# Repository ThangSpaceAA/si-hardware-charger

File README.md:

# st-hardware-charger
phần cứng mạch sạc pin năng lượng mặt trời

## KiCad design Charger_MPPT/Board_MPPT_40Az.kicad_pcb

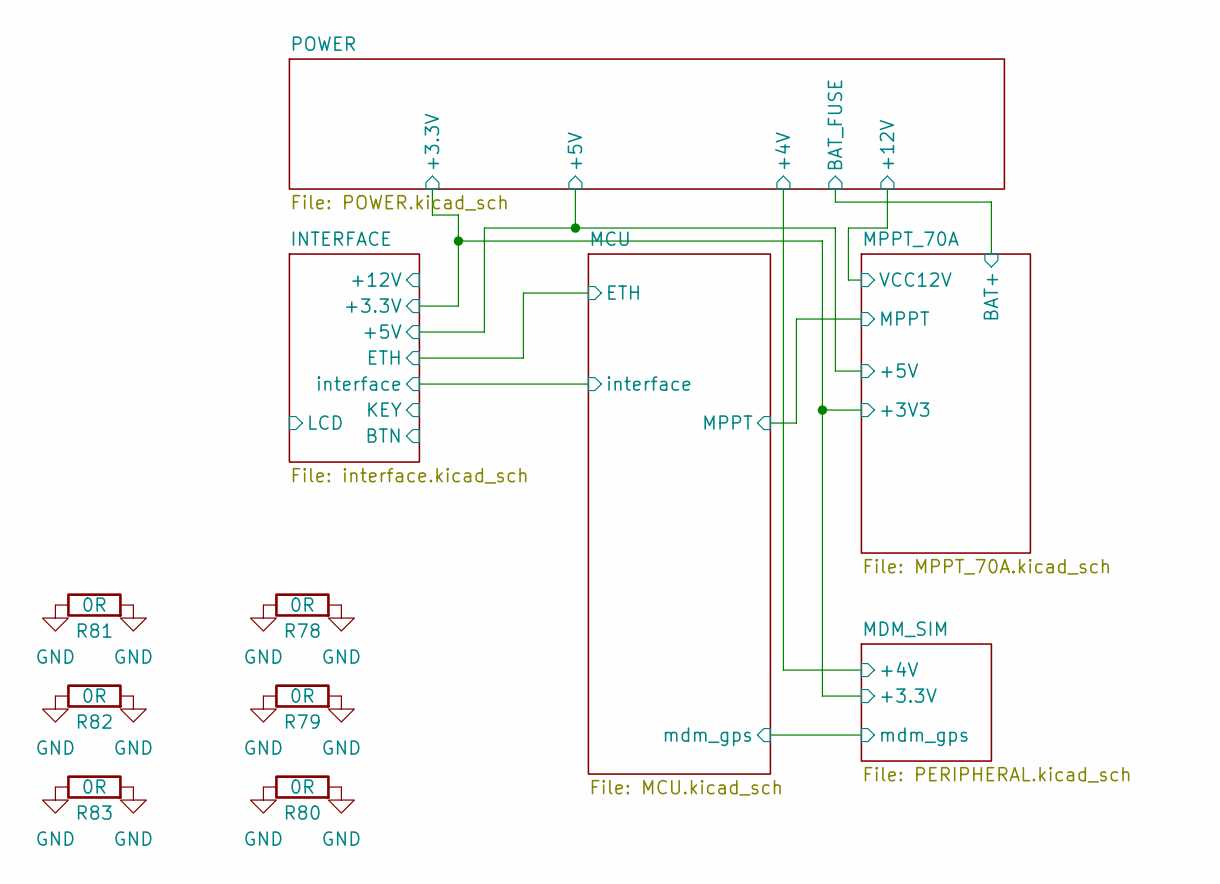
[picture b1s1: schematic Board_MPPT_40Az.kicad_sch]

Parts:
R78, R79, R80, R81, R82, R83: 0R; R_1206_3216Metric

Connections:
GND: R78.1, R78.2, R79.1, R79.2, R80.1, R80.2, R81.1, R81.2, R82.1, R82.2, R83.1, R83.2; also elsewhere on the board

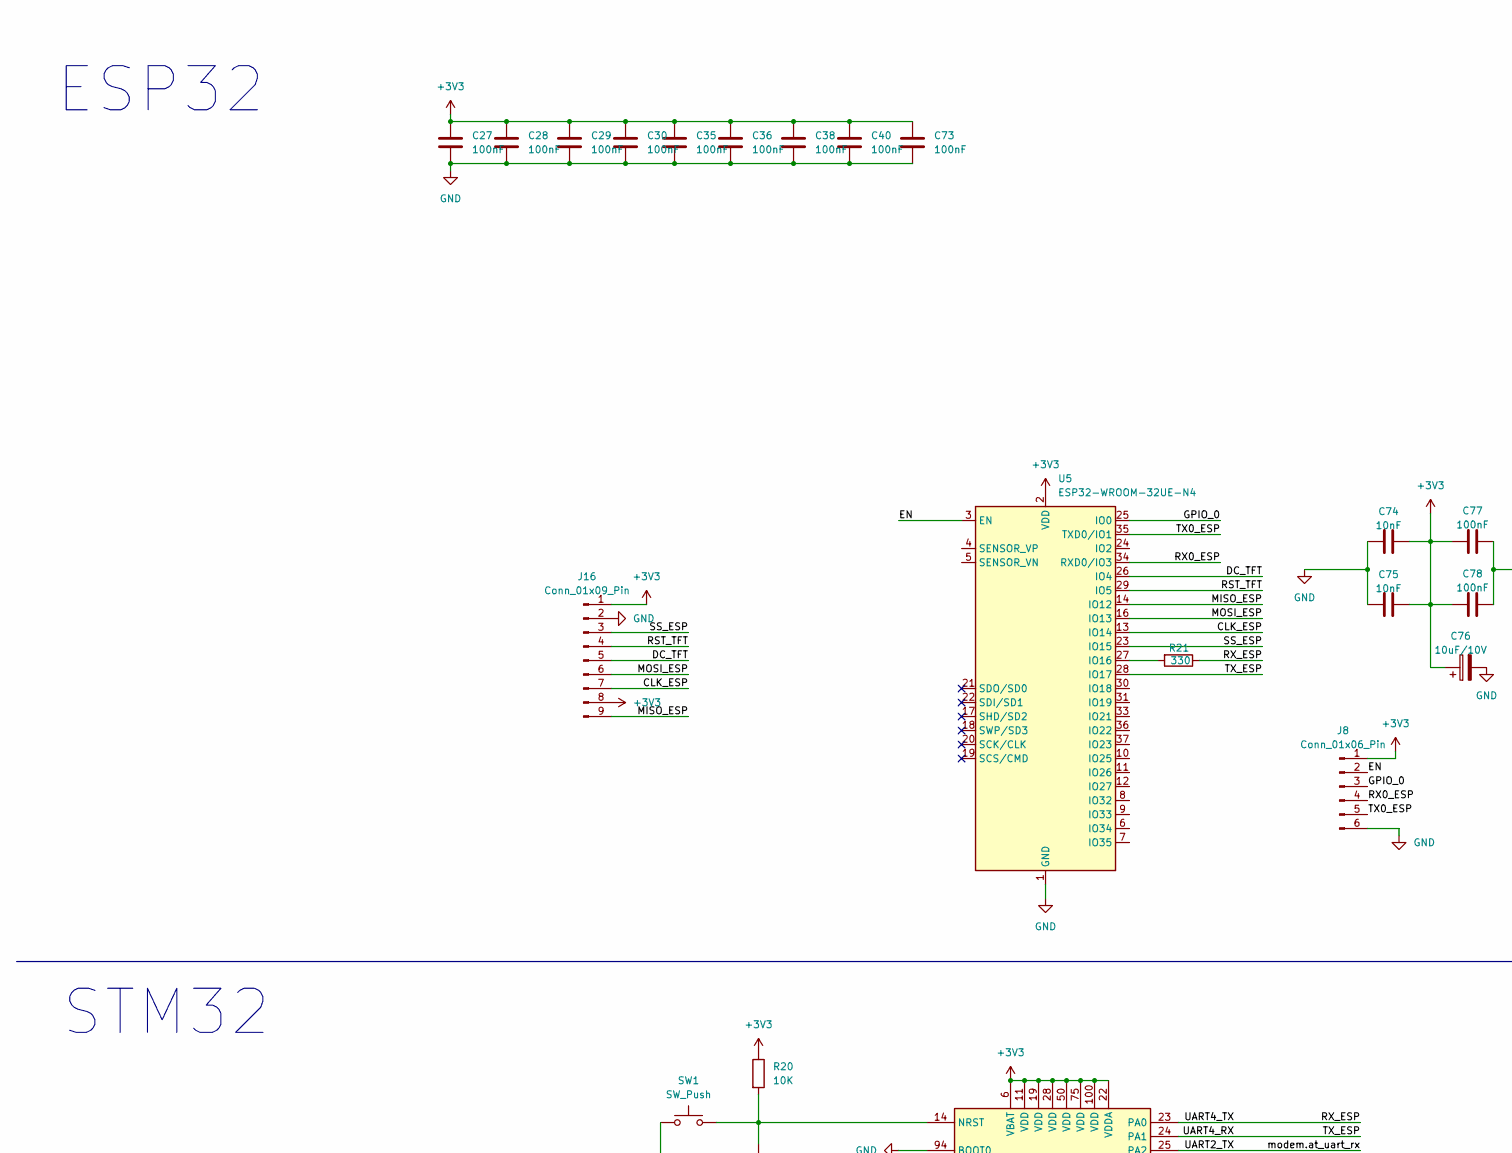
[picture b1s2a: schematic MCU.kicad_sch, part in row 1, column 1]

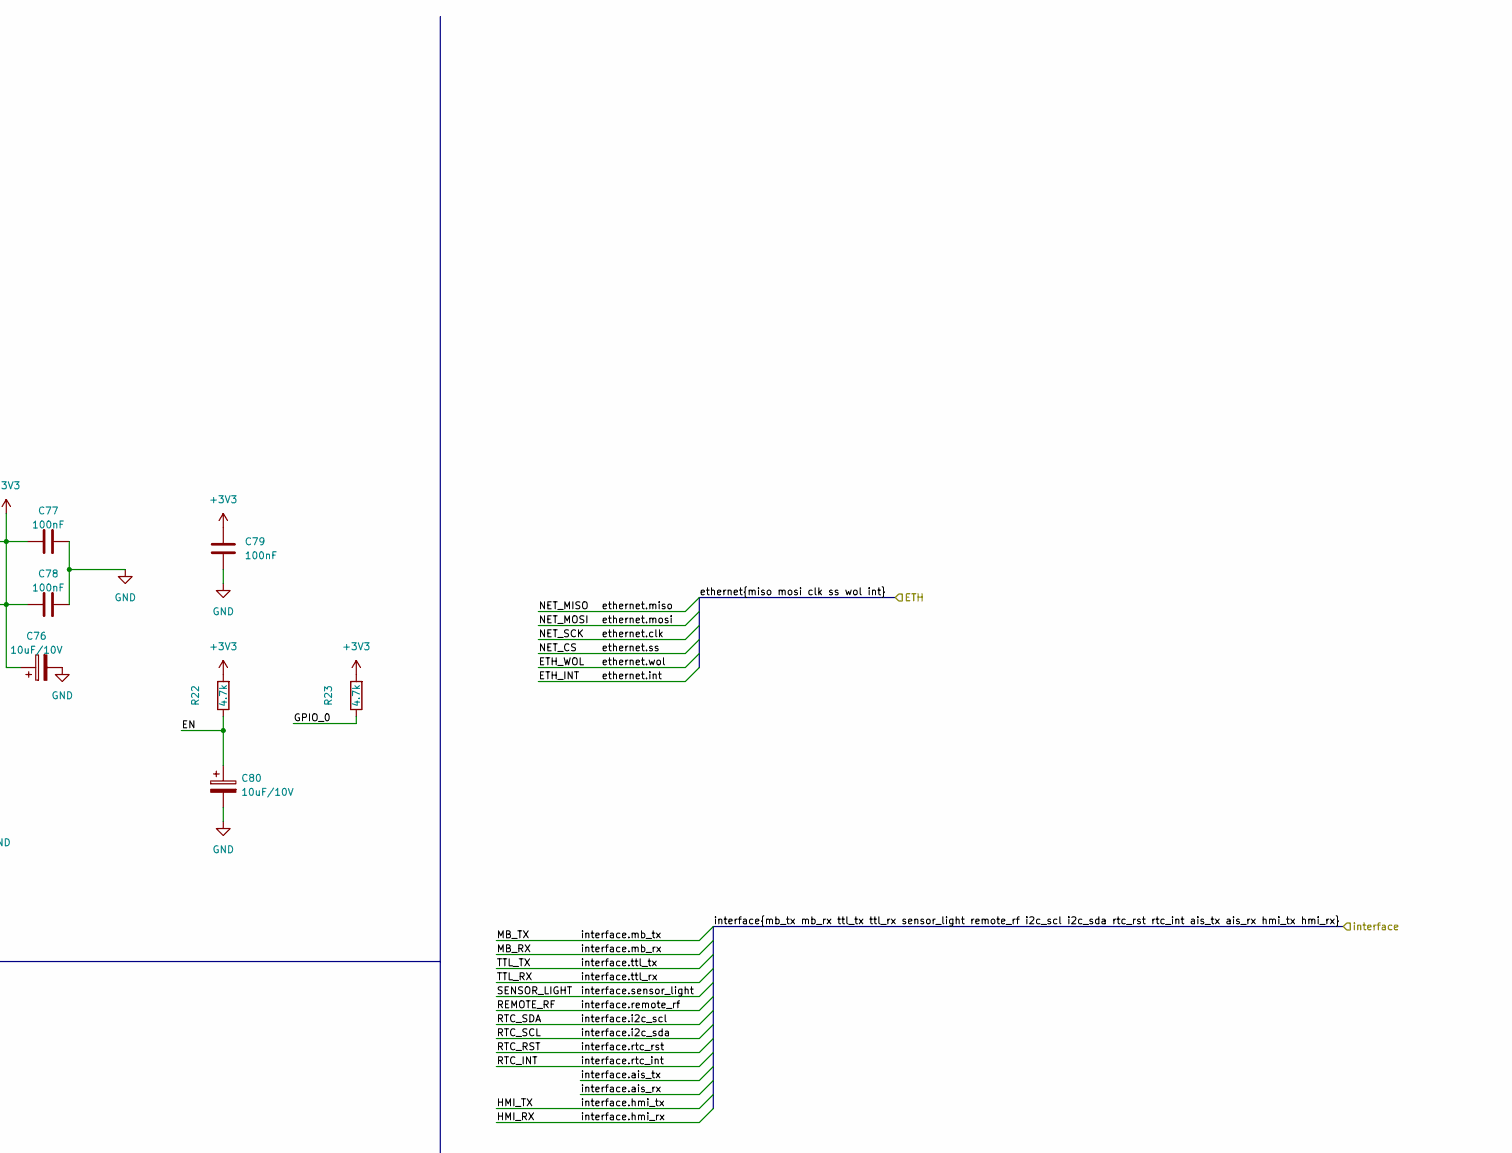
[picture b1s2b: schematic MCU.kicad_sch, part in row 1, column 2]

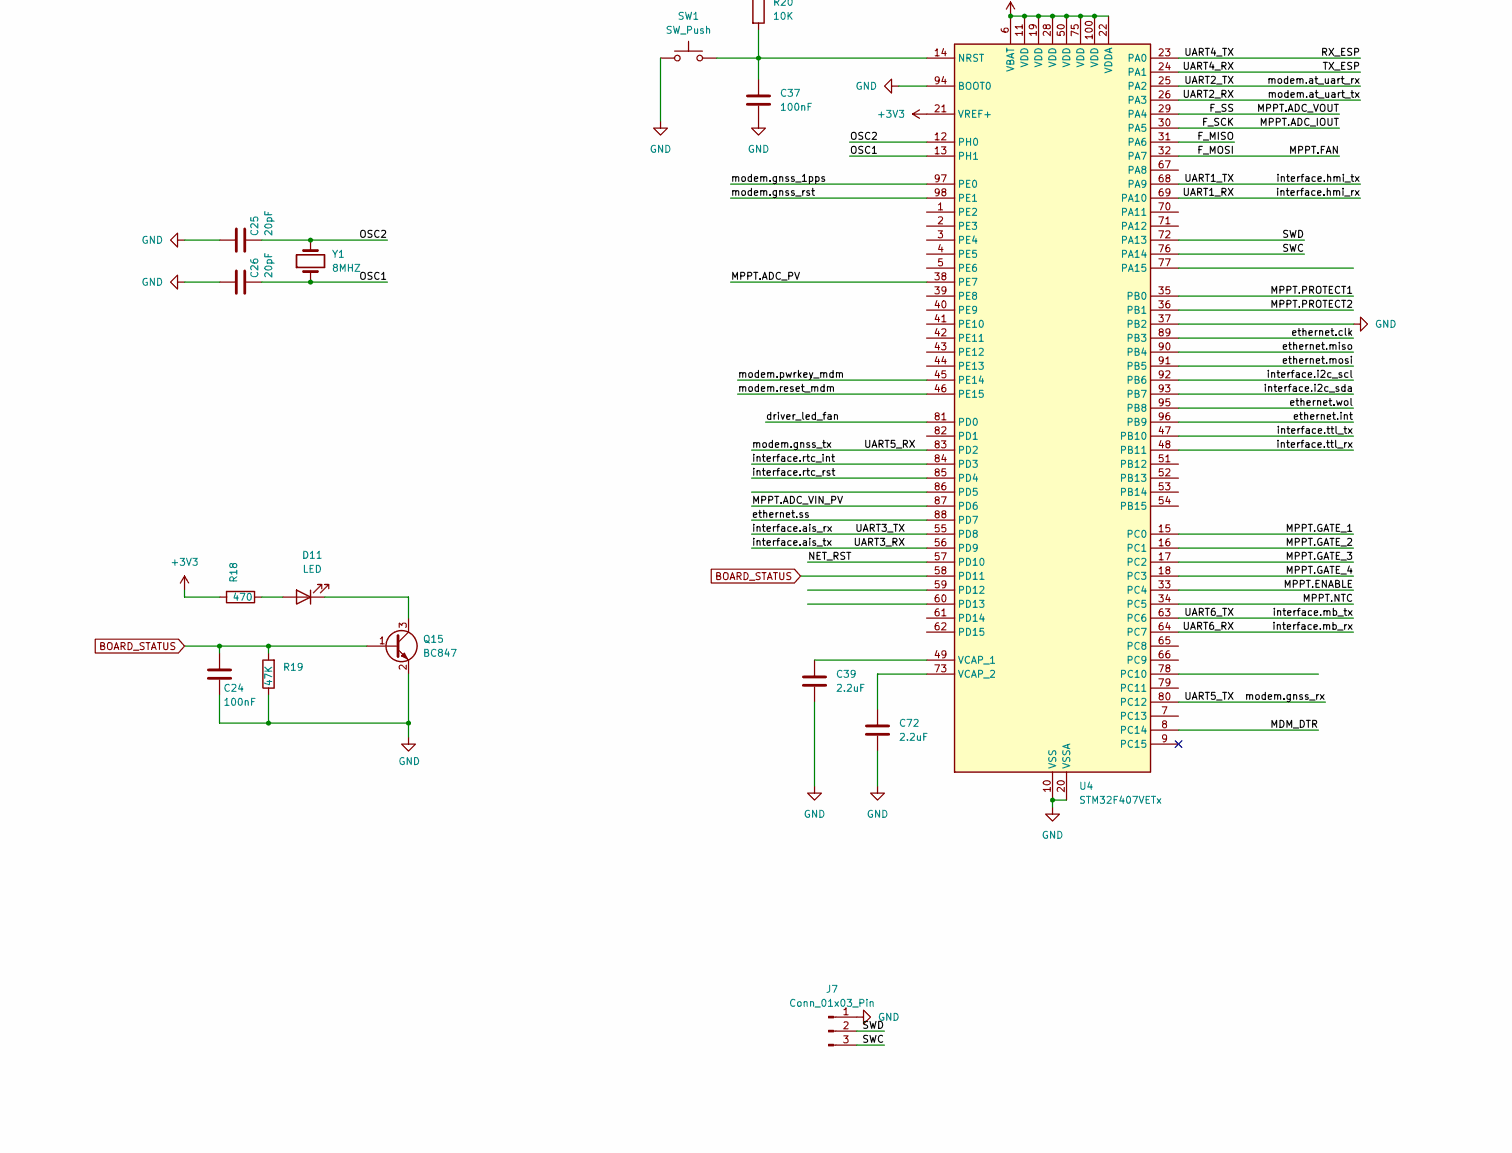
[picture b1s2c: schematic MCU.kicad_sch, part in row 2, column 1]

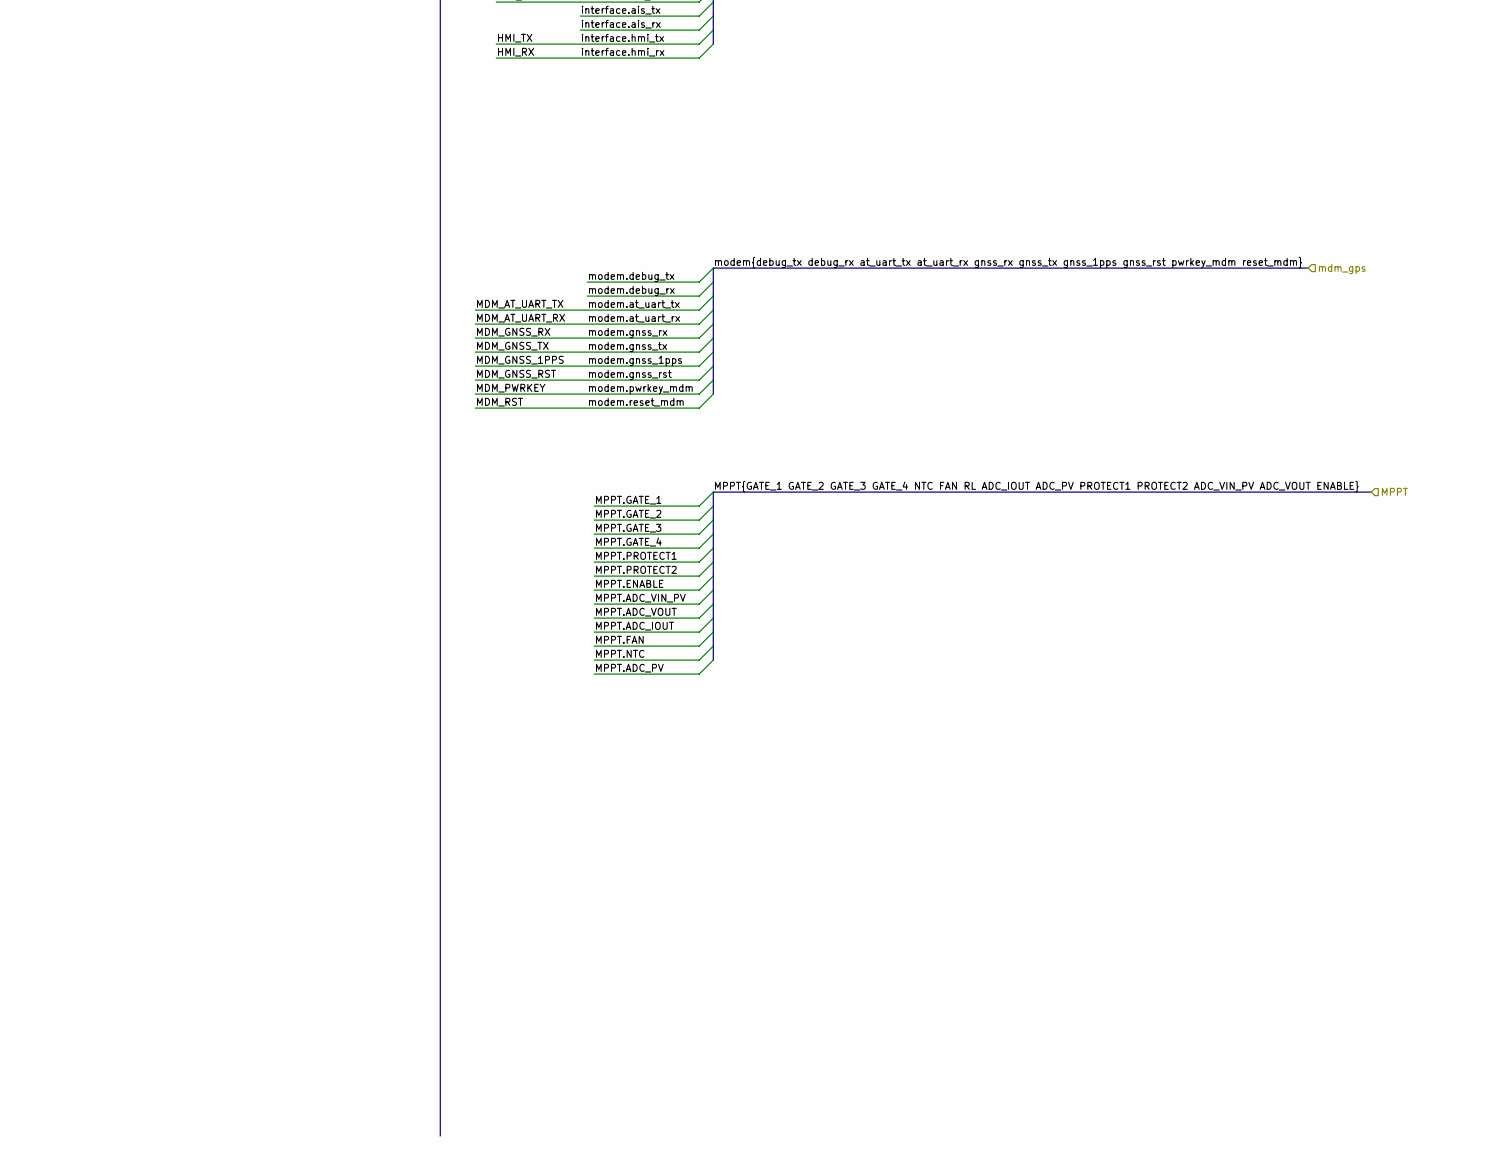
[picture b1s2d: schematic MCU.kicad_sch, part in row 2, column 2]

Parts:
C24, C27, C28, C29, C30, C35, C36, C37, C38, C40, C73, C77, C78, C79: 100nF; C_0805_2012Metric
C25, C26: 20pF; C_0402_1005Metric
C39, C72: 2.2uF; C_0805_2012Metric
C74, C75: 10nF; C_0805_2012Metric
C76, C80: 10uF/10V; CP_EIA-3216-18_Kemet-A
D11: LED; LED_0805_2012Metric
J7: Conn_01x03_Pin; PinHeader_1x03_P2.54mm_Vertical
J8: Conn_01x06_Pin; PinHeader_1x06_P2.54mm_Vertical
J16: Conn_01x09_Pin; PinHeader_1x09_P2.54mm_Vertical
Q15: BC847; SOT-23
R18: 470; R_0805_2012Metric
R19: 47K; R_0805_2012Metric
R20: 10K; R_0805_2012Metric
R21: 330; R_0805_2012Metric
R22, R23: 4.7k; R_0603_1608Metric
SW1: SW_Push; SW_SPST_CK_RS282G05A3
U4: STM32F407VETx; LQFP-100_14x14mm_P0.5mm
U5: ESP32-WROOM-32UE-N4; ESP32-WROOM-32U
Y1: 8MHZ; Crystal_SMD_Abracon_ABM7-2Pin_6.0x3.5mm

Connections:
+3V3: C27.1, C28.1, C29.1, C30.1, C35.1, C36.1, C38.1, C40.1, C73.1, C74.2, C75.2, C76.1, C77.1, C78.1, C79.2, J8.1, J16.1, J16.8, R18.2, R20.1, R22.2, R23.2, U4.6 (VBAT), U4.11 (VDD), U4.19 (VDD), U4.21 (VREF+), U4.22 (VDDA), U4.28 (VDD), U4.50 (VDD), U4.75 (VDD), U4.100 (VDD), U5.2 (VDD); also elsewhere on the board
/INTERFACE/ethernet.clk: U4.89 (PB3); also elsewhere on the board
/INTERFACE/ethernet.int: U4.96 (PB9); also elsewhere on the board
/INTERFACE/ethernet.miso: U4.90 (PB4); also elsewhere on the board
/INTERFACE/ethernet.mosi: U4.91 (PB5); also elsewhere on the board
/INTERFACE/ethernet.ss: U4.88 (PD7); also elsewhere on the board
/INTERFACE/ethernet.wol: U4.95 (PB8); also elsewhere on the board
/INTERFACE/interface.ais_rx: U4.55 (PD8); also elsewhere on the board
/INTERFACE/interface.ais_tx: U4.56 (PD9); also elsewhere on the board
/INTERFACE/interface.hmi_rx: U4.69 (PA10); also elsewhere on the board
/INTERFACE/interface.hmi_tx: U4.68 (PA9); also elsewhere on the board
/INTERFACE/interface.i2c_scl: U4.92 (PB6); also elsewhere on the board
/INTERFACE/interface.i2c_sda: U4.93 (PB7); also elsewhere on the board
/INTERFACE/interface.mb_rx: U4.64 (PC7); also elsewhere on the board
/INTERFACE/interface.mb_tx: U4.63 (PC6); also elsewhere on the board
/INTERFACE/interface.rtc_int: U4.84 (PD3); also elsewhere on the board
/INTERFACE/interface.rtc_rst: U4.85 (PD4); also elsewhere on the board
/INTERFACE/interface.ttl_rx: U4.48 (PB11); also elsewhere on the board
/INTERFACE/interface.ttl_tx: U4.47 (PB10); also elsewhere on the board
/MCU/CLK_ESP: J16.7, U5.13 (IO14)
/MCU/DC_TFT: J16.5, U5.26 (IO4)
/MCU/EN: C80.1, J8.2, R22.1, U5.3 (EN)
/MCU/F_MISO: U4.31 (PA6)
/MCU/GPIO_0: J8.3, R23.1, U5.25 (IO0)
/MCU/MDM_DTR: U4.8 (PC14)
/MCU/MISO_ESP: J16.9, U5.14 (IO12)
/MCU/MOSI_ESP: J16.6, U5.16 (IO13)
/MCU/MPPT.ADC_IOUT: U4.30 (PA5); also elsewhere on the board
/MCU/MPPT.ADC_PV: U4.38 (PE7); also elsewhere on the board
/MCU/MPPT.ADC_VIN_PV: U4.87 (PD6); also elsewhere on the board
/MCU/MPPT.ADC_VOUT: U4.29 (PA4); also elsewhere on the board
/MCU/MPPT.ENABLE: U4.33 (PC4); also elsewhere on the board
/MCU/MPPT.FAN: U4.32 (PA7); also elsewhere on the board
/MCU/MPPT.GATE_1: U4.15 (PC0); also elsewhere on the board
/MCU/MPPT.GATE_2: U4.16 (PC1); also elsewhere on the board
/MCU/MPPT.GATE_3: U4.17 (PC2); also elsewhere on the board
/MCU/MPPT.GATE_4: U4.18 (PC3); also elsewhere on the board
/MCU/MPPT.NTC: U4.34 (PC5); also elsewhere on the board
/MCU/MPPT.PROTECT1: U4.35 (PB0); also elsewhere on the board
/MCU/MPPT.PROTECT2: U4.36 (PB1); also elsewhere on the board
/MCU/NET_RST: U4.57 (PD10)
/MCU/OSC1: C26.2, U4.13 (PH1), Y1.1
/MCU/OSC2: C25.2, U4.12 (PH0), Y1.2
/MCU/RST_TFT: J16.4, U5.29 (IO5)
/MCU/RX0_ESP: J8.4, U5.34 (RXD0/IO3)
/MCU/RX_ESP: R21.1, U4.23 (PA0)
/MCU/SS_ESP: J16.3, U5.23 (IO15)
/MCU/SWC: J7.3, U4.76 (PA14)
/MCU/SWD: J7.2, U4.72 (PA13)
/MCU/TX0_ESP: J8.5, U5.35 (TXD0/IO1)
/MCU/TX_ESP: U4.24 (PA1), U5.28 (IO17)
/MCU/driver_led_fan: U4.81 (PD0)
/MCU/modem.at_uart_rx: U4.25 (PA2); also elsewhere on the board
/MCU/modem.at_uart_tx: U4.26 (PA3); also elsewhere on the board
/MCU/modem.gnss_1pps: U4.97 (PE0); also elsewhere on the board
/MCU/modem.gnss_rst: U4.98 (PE1); also elsewhere on the board
/MCU/modem.gnss_rx: U4.80 (PC12); also elsewhere on the board
/MCU/modem.gnss_tx: U4.83 (PD2); also elsewhere on the board
/MCU/modem.pwrkey_mdm: U4.45 (PE14); also elsewhere on the board
/MCU/modem.reset_mdm: U4.46 (PE15); also elsewhere on the board
BOARD_STATUS: C24.1, Q15.1 (B), R19.2, U4.58 (PD11)
GND: C24.2, C25.1, C26.1, C27.2, C28.2, C29.2, C30.2, C35.2, C36.2, C37.2, C38.2, C39.2, C40.2, C72.2, C73.2, C74.1, C75.1, C76.2, C77.2, C78.2, C79.1, C80.2, J7.1, J8.6, J16.2, Q15.2 (E), R19.1, SW1.1, U4.10 (VSS), U4.20 (VSSA), U4.27 (VSS), U4.37 (PB2), U4.74 (VSS), U4.94 (BOOT0), U4.99 (VSS), U5.1 (GND), U5.15 (GND), U5.38 (GND), U5.39 (GND); also elsewhere on the board
unnamed: D11.2 (A), R18.1
unnamed: D11.1 (K), Q15.3 (C)
unnamed: C37.1, R20.2, SW1.2, U4.14 (NRST)
unnamed: C39.1, U4.49 (VCAP_1)
unnamed: C72.1, U4.73 (VCAP_2)
unnamed: R21.2, U5.27 (IO16)

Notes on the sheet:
ESP32
STM32

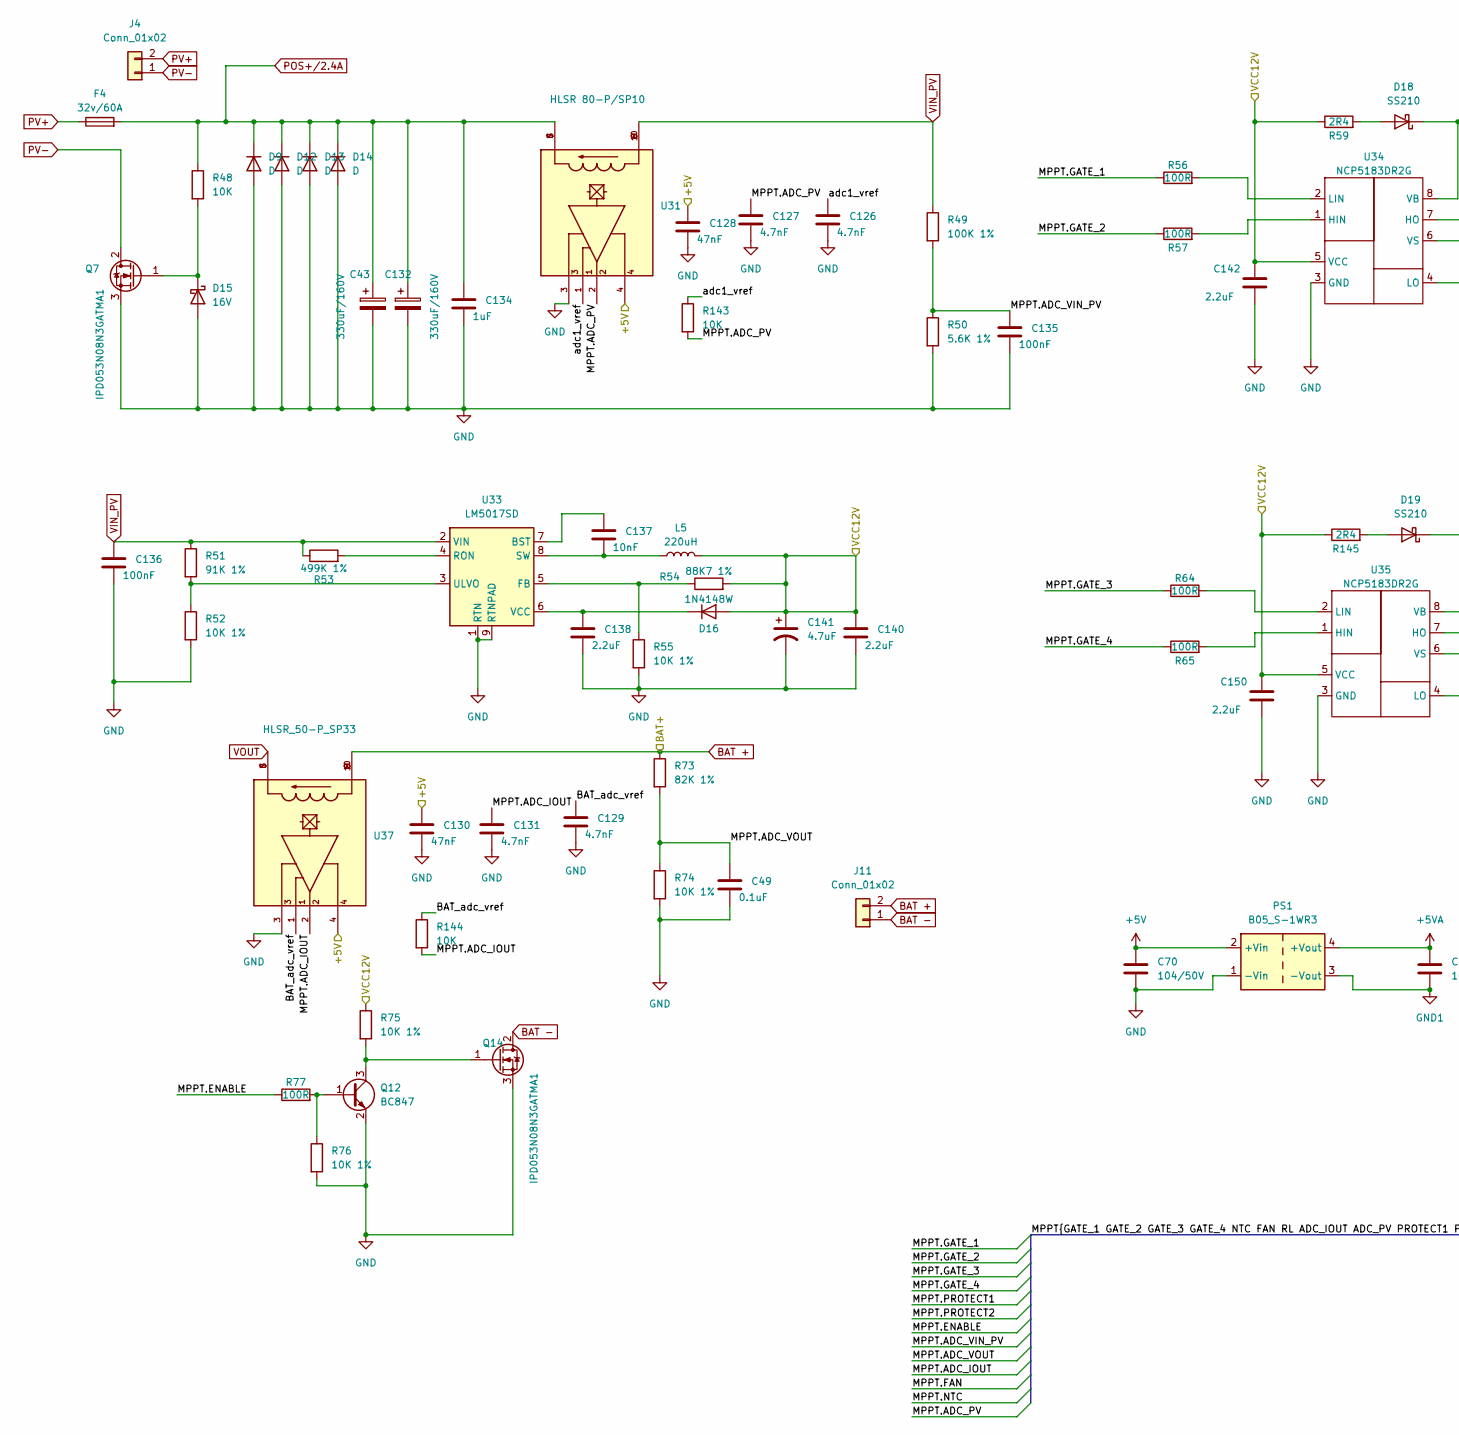
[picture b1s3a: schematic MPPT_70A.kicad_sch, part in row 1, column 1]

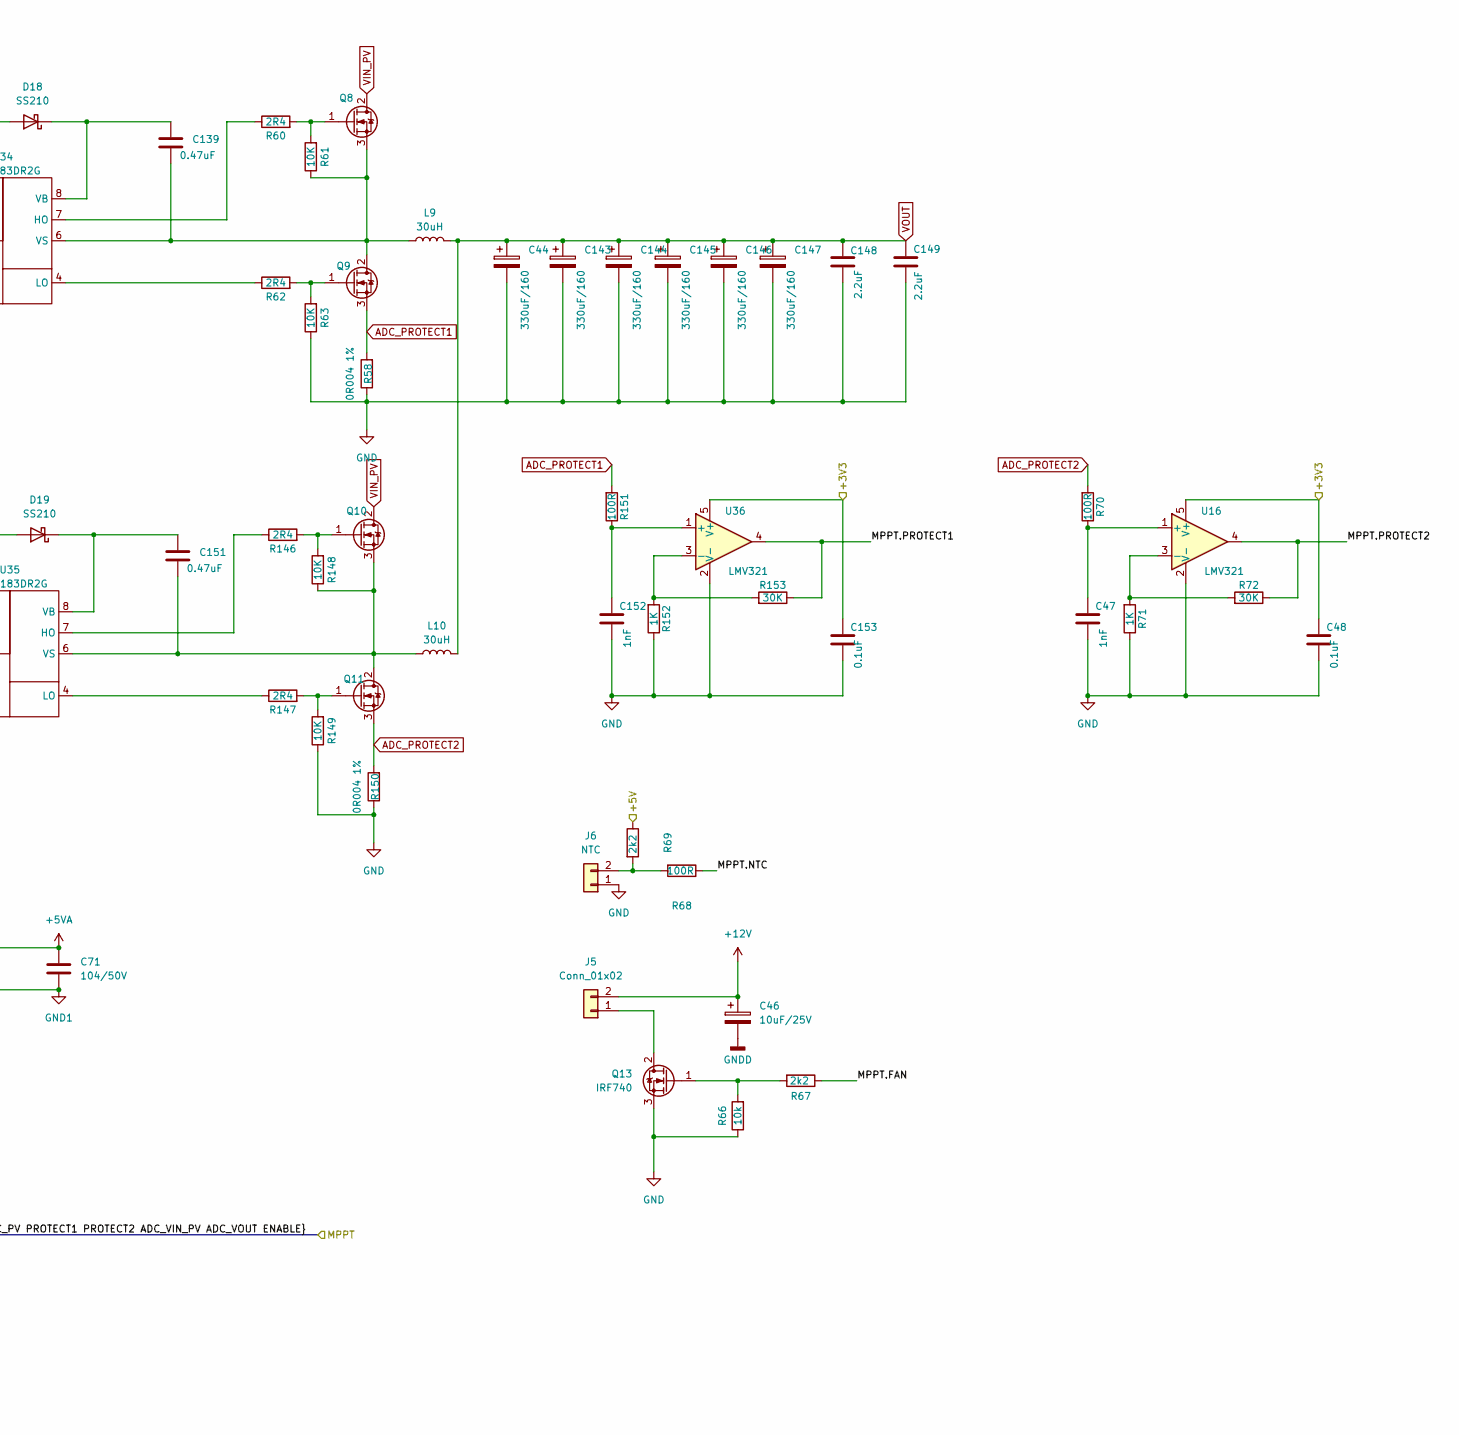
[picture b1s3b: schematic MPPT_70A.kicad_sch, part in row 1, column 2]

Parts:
C43, C132: 330uF/160V; C_Radial_D16.0mm_H25.0mm_P7.50mm
C44, C143, C144, C145, C146, C147: 330uF/160; C_Radial_D18.0mm_H35.5mm_P7.50mm
C46: 10uF/25V; CP_EIA-3216-12_Kemet-S
C47, C152: 1nF; C_1206_3216Metric_Pad1.33x1.80mm_HandSolder
C48, C153: 0.1uF; C_1206_3216Metric_Pad1.33x1.80mm_HandSolder
C49: 0.1uF; C_0805_2012Metric
C70, C71: 104/50V; C_0805_2012Metric
C126, C127, C129, C131: 4.7nF; C_0805_2012Metric
C128, C130: 47nF; C_0805_2012Metric
C134: 1uF; C_1206_3216Metric_Pad1.33x1.80mm_HandSolder
C135, C136: 100nF; C_0805_2012Metric
C137: 10nF; C_0805_2012Metric
C138, C140: 2.2uF; C_0805_2012Metric
C139, C151: 0.47uF; C_1206_3216Metric_Pad1.33x1.80mm_HandSolder
C141: 4.7uF; CP_EIA-3528-12_Kemet-T
C142, C148, C149, C150: 2.2uF; C_1206_3216Metric_Pad1.33x1.80mm_HandSolder
D9, D12, D13, D14: D; D_DO-201AD_P15.24mm_Horizontal
D15: 16V; D_SOD-123
D16: 1N4148W; D_MiniMELF
D18, D19: SS210; D_SMA
F4: 32v/60A; FUSE_50A
J4, J11: Conn_01x02; TerminalBlock_Dinkle_DT-55-B01X-02_P10.00mm
J5: Conn_01x02; Molex_KK-254_AE-6410-02A_1x02_P2.54mm_Vertical
J6: NTC; Molex_KK-254_AE-6410-02A_1x02_P2.54mm_Vertical
L5: 220uH; L_Cenker_CKCS6028
L9, L10: 30uH; L_Radial_D29.8mm_P29.30mm_Murata_1400series
PS1: B05_S-1WR3; MORNSUN_B0505S_1WR3
Q7, Q8, Q9, Q10, Q11, Q14: IPD053N08N3GATMA1; TO-252-2
Q12: BC847; SOT-23
Q13: IRF740; TO-220-3_Vertical
R48: 10K; R_1206_3216Metric
R49: 100K 1%; R_0805_2012Metric
R50: 5.6K 1%; R_0805_2012Metric
R51: 91K 1%; R_0805_2012Metric
R52, R55, R74, R75, R76: 10K 1%; R_0805_2012Metric
R53: 499K 1%; R_0805_2012Metric
R54: 88K7 1%; R_0805_2012Metric
R56, R57, R64, R65, R68, R70, R77, R151: 100R; R_0805_2012Metric
R58, R150: 0R004 1%; R_2512_6332Metric
R59, R60, R62, R145, R146, R147: 2R4; R_0805_2012Metric
R61, R63, R143, R144, R148, R149: 10K; R_0805_2012Metric
R66: 10k; R_0805_2012Metric
R67, R69: 2k2; R_0805_2012Metric
R71, R152: 1K; R_0805_2012Metric
R72, R153: 30K; R_0805_2012Metric
R73: 82K 1%; R_0805_2012Metric
U16, U36: LMV321; SOT-23-5_HandSoldering
U31: HLSR 80-P/SP10; XDCR_HLSR_50-P_SP33; PARTREV 24-September-2020/Version 8
U33: LM5017SD; WSON-8-1EP_4x4mm_P0.8mm_EP1.98x3mm
U34, U35: NCP5183DR2G; SOIC-8_3.9x4.9mm_P1.27mm
U37: HLSR_50-P_SP33; XDCR_HLSR_50-P_SP33; PARTREV 24-September-2020/Version 8

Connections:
+3V3: C48.1, C153.1, U16.5 (V+), U36.5 (V+); also elsewhere on the board
+5V: C70.2, C128.1, C130.1, PS1.2 (+Vin), R69.1, U31.4, U37.4; also elsewhere on the board
+5VA: C71.2, PS1.4 (+Vout)
+12V: C46.1, C140.1, C141.1, C142.1, C150.1, D16.2 (A), J5.2, L5.2, R54.2, R59.1, R75.1, R145.1, U34.5 (VCC), U35.5 (VCC); also elsewhere on the board
/MCU/MPPT.ADC_IOUT: C131.1, R144.2, U37.2; also elsewhere on the board
/MCU/MPPT.ADC_PV: C127.1, R143.2, U31.2; also elsewhere on the board
/MCU/MPPT.ADC_VIN_PV: C135.1, R49.2, R50.1; also elsewhere on the board
/MCU/MPPT.ADC_VOUT: C49.1, R73.2, R74.1; also elsewhere on the board
/MCU/MPPT.ENABLE: R77.1; also elsewhere on the board
/MCU/MPPT.FAN: R67.1; also elsewhere on the board
/MCU/MPPT.GATE_1: R56.1; also elsewhere on the board
/MCU/MPPT.GATE_2: R57.1; also elsewhere on the board
/MCU/MPPT.GATE_3: R64.1; also elsewhere on the board
/MCU/MPPT.GATE_4: R65.1; also elsewhere on the board
/MCU/MPPT.NTC: R68.1; also elsewhere on the board
/MCU/MPPT.PROTECT1: R153.1, U36.4; also elsewhere on the board
/MCU/MPPT.PROTECT2: R72.1, U16.4; also elsewhere on the board
/MPPT_70A/BAT_adc_vref: C129.1, R144.1, U37.1
/MPPT_70A/adc1_vref: C126.1, R143.1, U31.1
ADC_PROTECT1: Q9.3 (S), R58.2, R151.2
ADC_PROTECT2: Q11.3 (S), R70.2, R150.2
BAT +: J11.2, R73.1, U37.8, U37.9, U37.10; also elsewhere on the board
BAT -: J11.1, Q14.2 (D)
GND: C43.2, C44.2, C47.2, C48.2, C49.2, C70.1, C126.2, C127.2, C128.2, C129.2, C130.2, C131.2, C132.2, C134.2, C135.2, C136.2, C138.2, C140.2, C141.2, C142.2, C143.2, C144.2, C145.2, C146.2, C147.2, C148.2, C149.2, C150.2, C152.2, C153.2, D9.2 (A), D12.2 (A), D13.2 (A), D14.2 (A), D15.2 (A), J6.1, PS1.1 (-Vin), Q7.3 (S), Q12.2 (E), Q13.3 (S), Q14.3 (S), R50.2, R52.2, R55.2, R58.1, R63.1, R66.1, R71.1, R74.2, R76.2, R149.1, R150.1, R152.1, U16.2 (V-), U31.3, U33.1 (RTN), U33.9 (RTNPAD), U34.3 (GND), U35.3 (GND), U36.2 (V-), U37.3; also elsewhere on the board
GND1: C71.1, PS1.3 (-Vout)
GNDD: C46.2
unnamed: D15.1 (K), Q7.1 (G), R48.2
unnamed: C138.1, D16.1 (K), U33.6 (VCC)
unnamed: D18.2 (A), R59.2
unnamed: C139.1, D18.1 (K), U34.8 (VB)
unnamed: D19.2 (A), R145.2
unnamed: C151.1, D19.1 (K), U35.8 (VB)
unnamed: J5.1, Q13.2 (D)
unnamed: J6.2, R68.2, R69.2
unnamed: Q8.1 (G), R60.2, R61.2
unnamed: C139.2, L9.1, Q8.3 (S), Q9.2 (D), R61.1, U34.6 (VS)
unnamed: Q9.1 (G), R62.2, R63.2
unnamed: Q10.1 (G), R146.2, R148.2
unnamed: C151.2, L10.1, Q10.3 (S), Q11.2 (D), R148.1, U35.6 (VS)
unnamed: Q11.1 (G), R147.2, R149.2
unnamed: Q12.1 (B), R76.1, R77.2
unnamed: Q12.3 (C), Q14.1 (G), R75.2
unnamed: Q13.1 (G), R66.2, R67.2
unnamed: C47.1, R70.1, U16.1 (+)
unnamed: R71.2, R72.2, U16.3 (-)
unnamed: C137.1, U33.7 (BST)
unnamed: R54.1, R55.1, U33.5 (FB)
unnamed: R53.2, U33.4 (RON)
unnamed: C137.2, L5.1, U33.8 (SW)
unnamed: R51.2, R52.1, U33.3 (ULVO)
unnamed: R57.2, U34.1 (HIN)
unnamed: R60.1, U34.7 (HO)
unnamed: R56.2, U34.2 (LIN)
unnamed: R62.1, U34.4 (LO)
unnamed: R65.2, U35.1 (HIN)
unnamed: R146.1, U35.7 (HO)
unnamed: R64.2, U35.2 (LIN)
unnamed: R147.1, U35.4 (LO)
unnamed: C152.1, R151.1, U36.1 (+)
unnamed: R152.2, R153.2, U36.3 (-)
POS+/2.4A: C43.1, C132.1, C134.1, D9.1 (K), D12.1 (K), D13.1 (K), D14.1 (K), F4.2, R48.1, U31.5, U31.6, U31.7
PV+: F4.1, J4.2
PV-: J4.1, Q7.2 (D)
VIN_PV: C136.1, Q8.2 (D), Q10.2 (D), R49.1, R51.1, R53.1, U31.8, U31.9, U31.10, U33.2 (VIN)
VOUT: C44.1, C143.1, C144.1, C145.1, C146.1, C147.1, C148.1, C149.1, L9.2, L10.2, U37.5, U37.6, U37.7
